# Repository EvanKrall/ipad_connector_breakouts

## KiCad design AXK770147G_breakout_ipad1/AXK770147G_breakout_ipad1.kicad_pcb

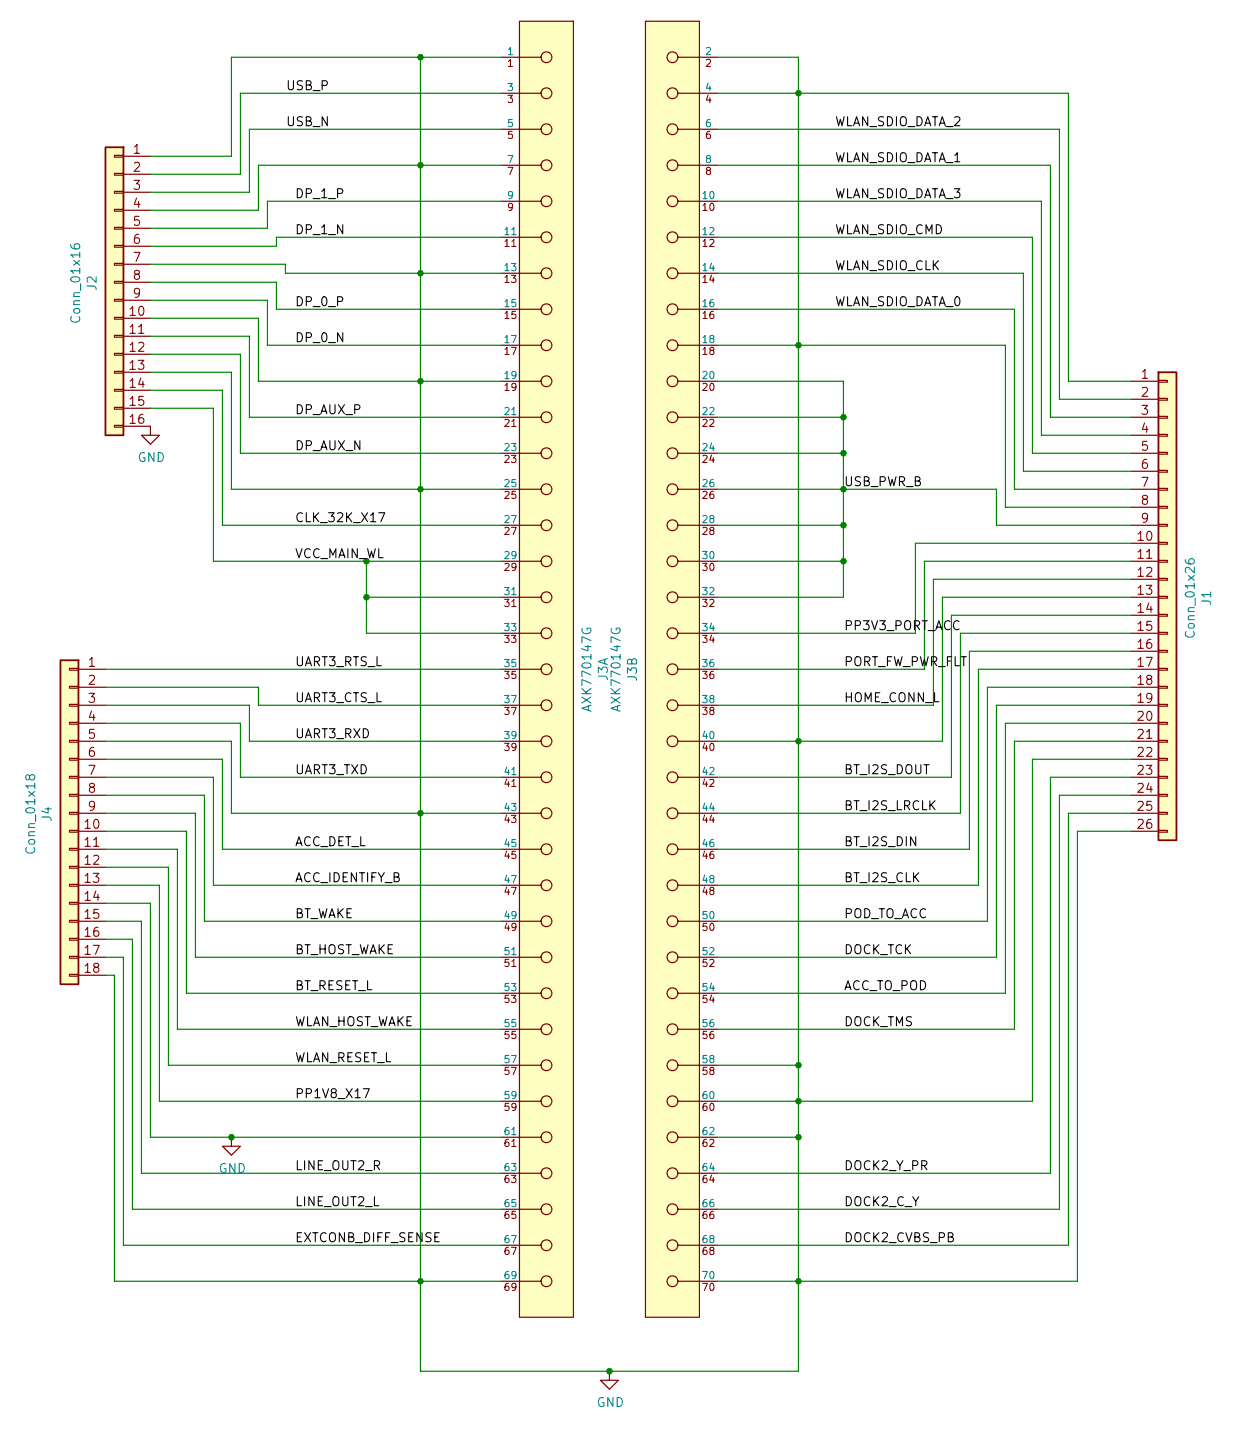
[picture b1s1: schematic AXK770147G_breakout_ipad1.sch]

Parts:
J1: Conn_01x26; PinHeader_2x13_P2.54mm_Vertical
J2: Conn_01x16; PinHeader_1x16_P2.54mm_Vertical
J3: AXK770147G; Panasonic-AXK770147G-MFG; current rating 0.3A; voltage rating 60V; mouser part number 769-AXK770147G; digikey description CONN SOCKET 70POS SMD GOLD
J4: Conn_01x18; PinHeader_1x18_P2.54mm_Vertical

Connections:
/ACC_DET_L: J3.45, J4.6
/ACC_IDENTIFY_B: J3.47, J4.7
/ACC_TO_POD: J1.20, J3.54
/BT_HOST_WAKE: J3.51, J4.9
/BT_I2S_CLK: J1.17, J3.48
/BT_I2S_DIN: J1.16, J3.46
/BT_I2S_DOUT: J1.14, J3.42
/BT_I2S_LRCLK: J1.15, J3.44
/BT_RESET_L: J3.53, J4.10
/BT_WAKE: J3.49, J4.8
/CLK_32K_X17: J2.14, J3.27
/DOCK2_CVBS_PB: J1.25, J3.68
/DOCK2_C_Y: J1.24, J3.66
/DOCK2_Y_PR: J1.23, J3.64
/DOCK_TCK: J1.19, J3.52
/DOCK_TMS: J1.21, J3.56
/DP_0_N: J2.9, J3.17
/DP_0_P: J2.8, J3.15
/DP_1_N: J2.6, J3.11
/DP_1_P: J2.5, J3.9
/DP_AUX_N: J2.12, J3.23
/DP_AUX_P: J2.11, J3.21
/EXTCONB_DIFF_SENSE: J3.67, J4.17
/HOME_CONN_L: J1.12, J3.38
/LINE_OUT2_L: J3.65, J4.16
/LINE_OUT2_R: J3.63, J4.15
/POD_TO_ACC: J1.18, J3.50
/PORT_FW_PWR_FLT: J1.11, J3.36
/PP1V8_X17: J3.59, J4.13
/PP3V3_PORT_ACC: J1.10, J3.34
/UART3_CTS_L: J3.37, J4.2
/UART3_RTS_L: J3.35, J4.1
/UART3_RXD: J3.39, J4.3
/UART3_TXD: J3.41, J4.4
/USB_N: J2.3, J3.5
/USB_P: J2.2, J3.3
/USB_PWR_B: J1.9, J3.20, J3.22, J3.24, J3.26, J3.28, J3.30, J3.32
/VCC_MAIN_WL: J2.15, J3.29, J3.31, J3.33
/WLAN_HOST_WAKE: J3.55, J4.11
/WLAN_RESET_L: J3.57, J4.12
/WLAN_SDIO_CLK: J1.6, J3.14
/WLAN_SDIO_CMD: J1.5, J3.12
/WLAN_SDIO_DATA_0: J1.7, J3.16
/WLAN_SDIO_DATA_1: J1.3, J3.8
/WLAN_SDIO_DATA_2: J1.2, J3.6
/WLAN_SDIO_DATA_3: J1.4, J3.10
GND: J1.1, J1.8, J1.13, J1.22, J1.26, J2.1, J2.4, J2.7, J2.10, J2.13, J2.16, J3.1, J3.2, J3.4, J3.7, J3.13, J3.18, J3.19, J3.25, J3.40, J3.43, J3.58, J3.60, J3.61, J3.62, J3.69, J3.70, J4.5, J4.14, J4.18

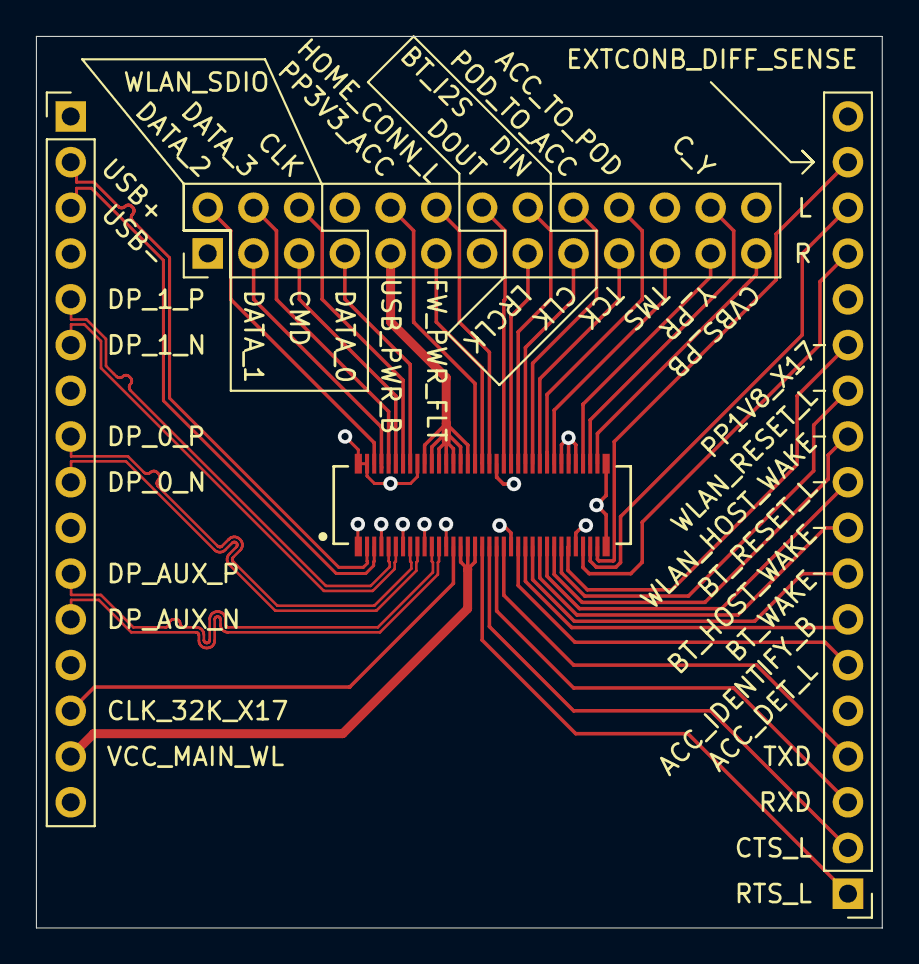
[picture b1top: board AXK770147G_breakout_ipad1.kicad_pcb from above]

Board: 4 copper layers, 47.0 x 49.5 mm, 4 parts (0 on the bottom side), 47 nets.

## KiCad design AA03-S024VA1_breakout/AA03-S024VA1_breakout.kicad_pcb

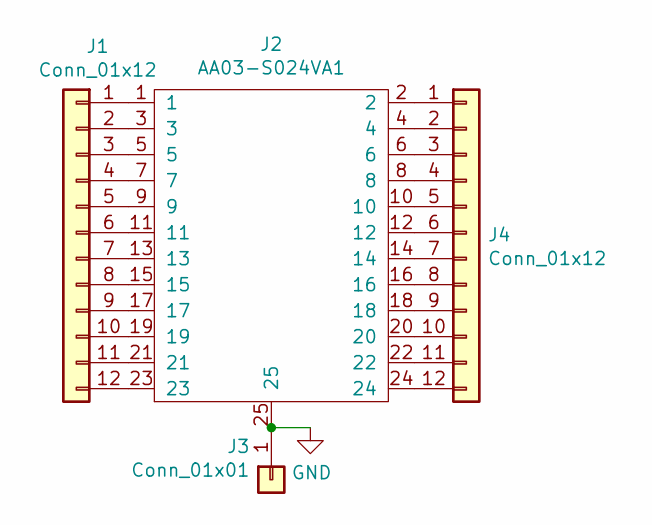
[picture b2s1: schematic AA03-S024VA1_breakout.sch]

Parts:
J1, J4: Conn_01x12; PinHeader_1x12_P2.54mm_Vertical
J2: AA03-S024VA1
J3: Conn_01x01; PinHeader_1x01_P2.54mm_Vertical

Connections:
GND: J2.25, J3.1
unnamed: J1.1, J2.1
unnamed: J1.2, J2.3
unnamed: J1.3, J2.5
unnamed: J1.4, J2.7
unnamed: J1.5, J2.9
unnamed: J1.6, J2.11
unnamed: J1.7, J2.13
unnamed: J1.8, J2.15
unnamed: J1.9, J2.17
unnamed: J1.10, J2.19
unnamed: J1.11, J2.21
unnamed: J1.12, J2.23
unnamed: J2.2, J4.1
unnamed: J2.4, J4.2
unnamed: J2.6, J4.3
unnamed: J2.8, J4.4
unnamed: J2.10, J4.5
unnamed: J2.12, J4.6
unnamed: J2.14, J4.7
unnamed: J2.16, J4.8
unnamed: J2.18, J4.9
unnamed: J2.20, J4.10
unnamed: J2.22, J4.11
unnamed: J2.24, J4.12

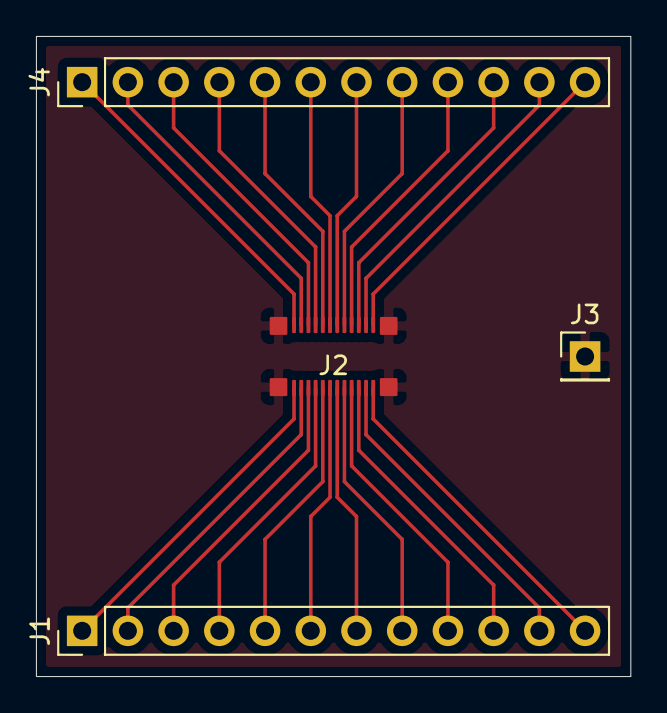
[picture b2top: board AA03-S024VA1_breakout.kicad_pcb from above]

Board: 2 copper layers, 33.0 x 35.6 mm, 4 parts (0 on the bottom side), 25 nets.

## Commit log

2021-02-21 Make breakout boards for the portrait dock connector and ambient light sensor
2021-02-21 Move traces around a bit to increase separation; add ground pins.
2021-02-23 A more complicated breakout board for the portrait dock connector
